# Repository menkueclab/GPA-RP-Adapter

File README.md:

# GPA-RP-Adapter
This is a shield for the red pitaya (rp-122 or rp-125) to connect it easily to the GPA-FHDO.

# Parts
- pin header
- RJ45 connector
- schmitt trigger (optional)
- SMA connector  (optional)
- capacitor  (optional)
- fan (optional)

for details see KiCad schematic.

# Contributing
Benjamin Menkuec

# Disclaimer
Not intended for medical use!

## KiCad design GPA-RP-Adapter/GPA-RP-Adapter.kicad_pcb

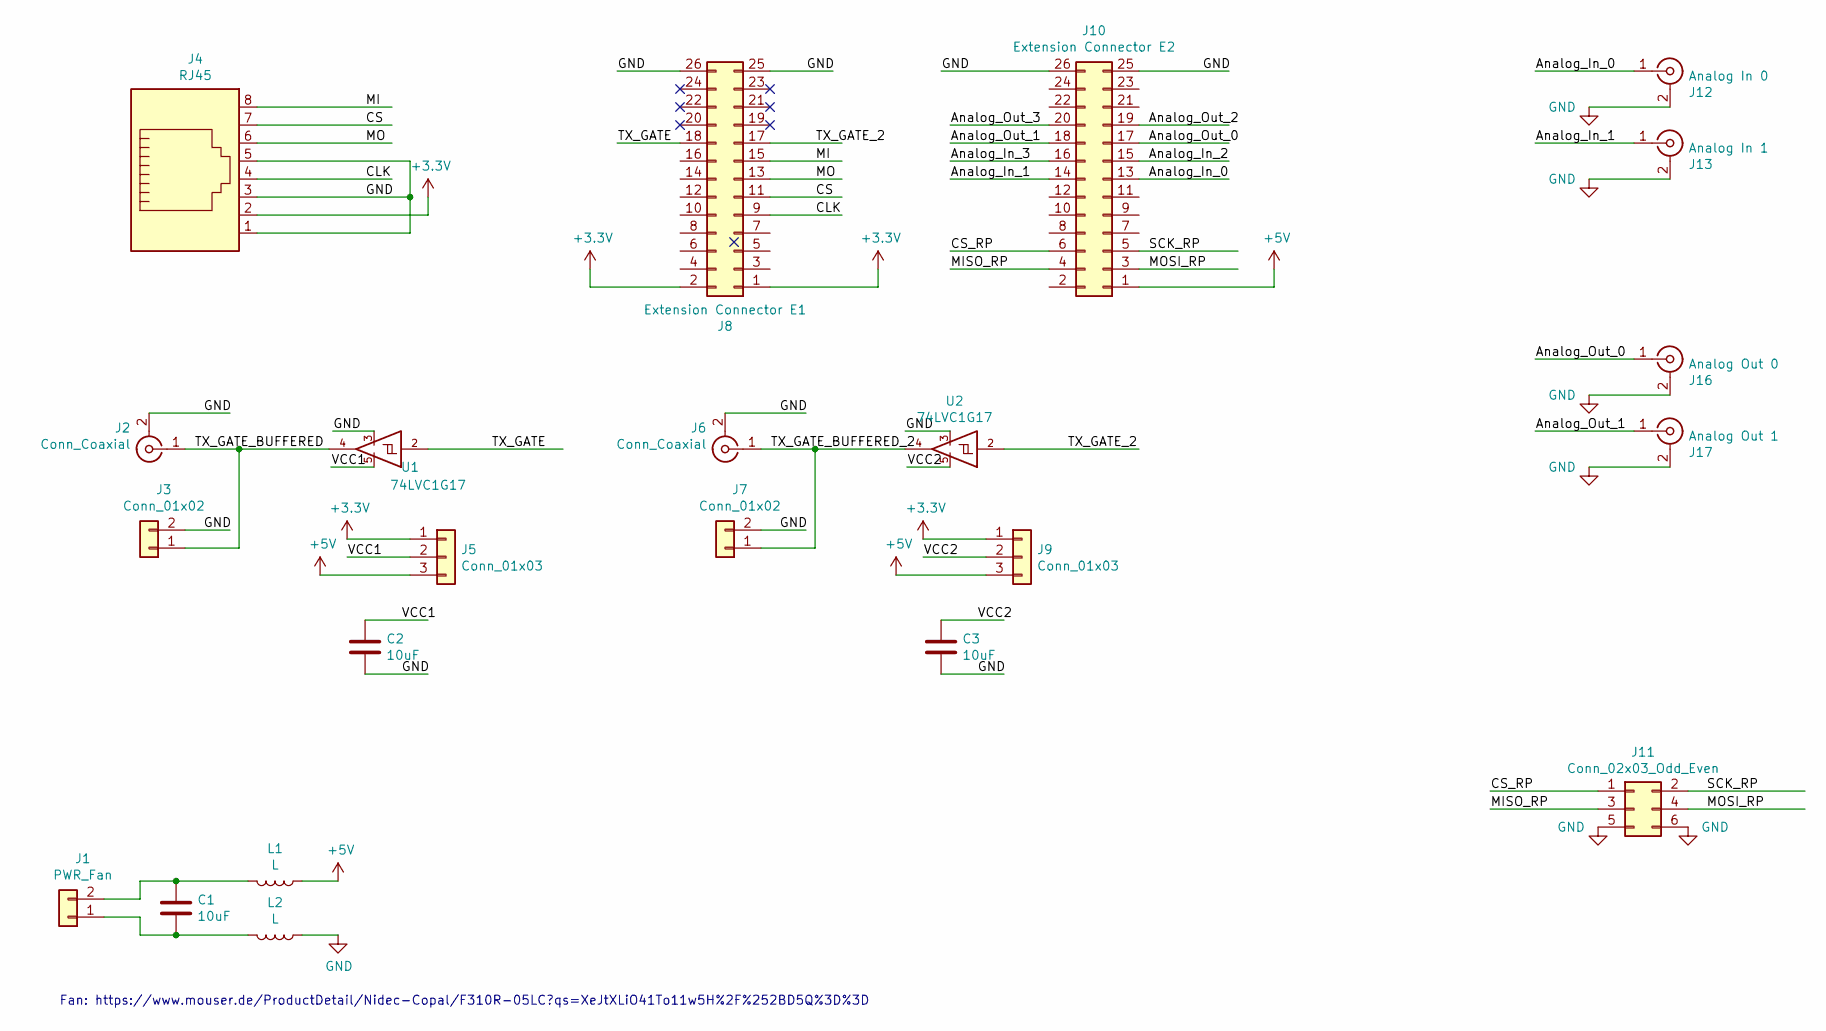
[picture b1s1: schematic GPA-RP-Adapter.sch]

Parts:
C1, C2, C3: 10uF; C_0805_2012Metric_Pad1.15x1.40mm_HandSolder
J1: PWR_Fan; PinHeader_1x02_P2.54mm_Vertical
J2, J6: Conn_Coaxial; SMA_Amphenol_132134_Vertical
J3, J7: Conn_01x02; PinHeader_1x02_P2.54mm_Vertical
J4: RJ45; RJ45_Amphenol_54602-x08_Horizontal
J5, J9: Conn_01x03; PinHeader_1x03_P2.54mm_Vertical
J8: Extension Connector E1; PinHeader_2x13_P2.54mm_Vertical
J10: Extension Connector E2; PinHeader_2x13_P2.54mm_Vertical
J11: Conn_02x03_Odd_Even; PinHeader_2x03_P2.54mm_Vertical
J12: Analog In 0; SMA_Amphenol_132134_Vertical
J13: Analog In 1; SMA_Amphenol_132134_Vertical
J16: Analog Out 0; SMA_Amphenol_132134_Vertical
J17: Analog Out 1; SMA_Amphenol_132134_Vertical
L1, L2: L; L_0805_2012Metric_Pad1.15x1.40mm_HandSolder
U1, U2: 74LVC1G17; SOT-23-5_HandSoldering

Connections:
+3V3: J4.2, J5.1, J8.1, J8.2, J9.1; also elsewhere on the board
+5V: J5.3, J9.3, J10.1, L1.1; also elsewhere on the board
/Analog_In_0: J10.13, J12.1 (In); also elsewhere on the board
/Analog_In_1: J10.14, J13.1 (In); also elsewhere on the board
/Analog_Out_0: J10.17, J16.1 (In); also elsewhere on the board
/Analog_Out_1: J10.18, J17.1 (In); also elsewhere on the board
/CLK: J4.4, J8.9; also elsewhere on the board
/CS: J4.7, J8.11; also elsewhere on the board
/CS_RP: J10.6, J11.1; also elsewhere on the board
/MI: J4.8, J8.15; also elsewhere on the board
/MISO_RP: J10.4, J11.3; also elsewhere on the board
/MO: J4.6, J8.13; also elsewhere on the board
/MOSI_RP: J10.3, J11.4; also elsewhere on the board
/SCK_RP: J10.5, J11.2; also elsewhere on the board
/TX_GATE: J8.18, U1.2; also elsewhere on the board
/TX_GATE_2: J8.17, U2.2; also elsewhere on the board
/TX_GATE_BUFFERED: J2.1 (In), J3.1, U1.4
/TX_GATE_BUFFERED_2: J6.1 (In), J7.1, U2.4
/VCC1: C2.1, J5.2, U1.5
/VCC2: C3.1, J9.2, U2.5
GND: C2.2, C3.2, J2.2 (Ext), J3.2, J4.1, J4.3, J4.5, J6.2 (Ext), J7.2, J8.25, J8.26, J10.25, J10.26, J11.5, J11.6, J12.2 (Ext), J13.2 (Ext), J16.2 (Ext), J17.2 (Ext), L2.1, U1.3, U2.3; also elsewhere on the board
unnamed: C1.1, J1.2, L1.2
unnamed: C1.2, J1.1, L2.2

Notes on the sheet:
Fan: https://www.mouser.de/ProductDetail/Nidec-Copal/F310R-05LC?qs=XeJtXLiO41To11w5H%2F%252BD5Q%3D%3D

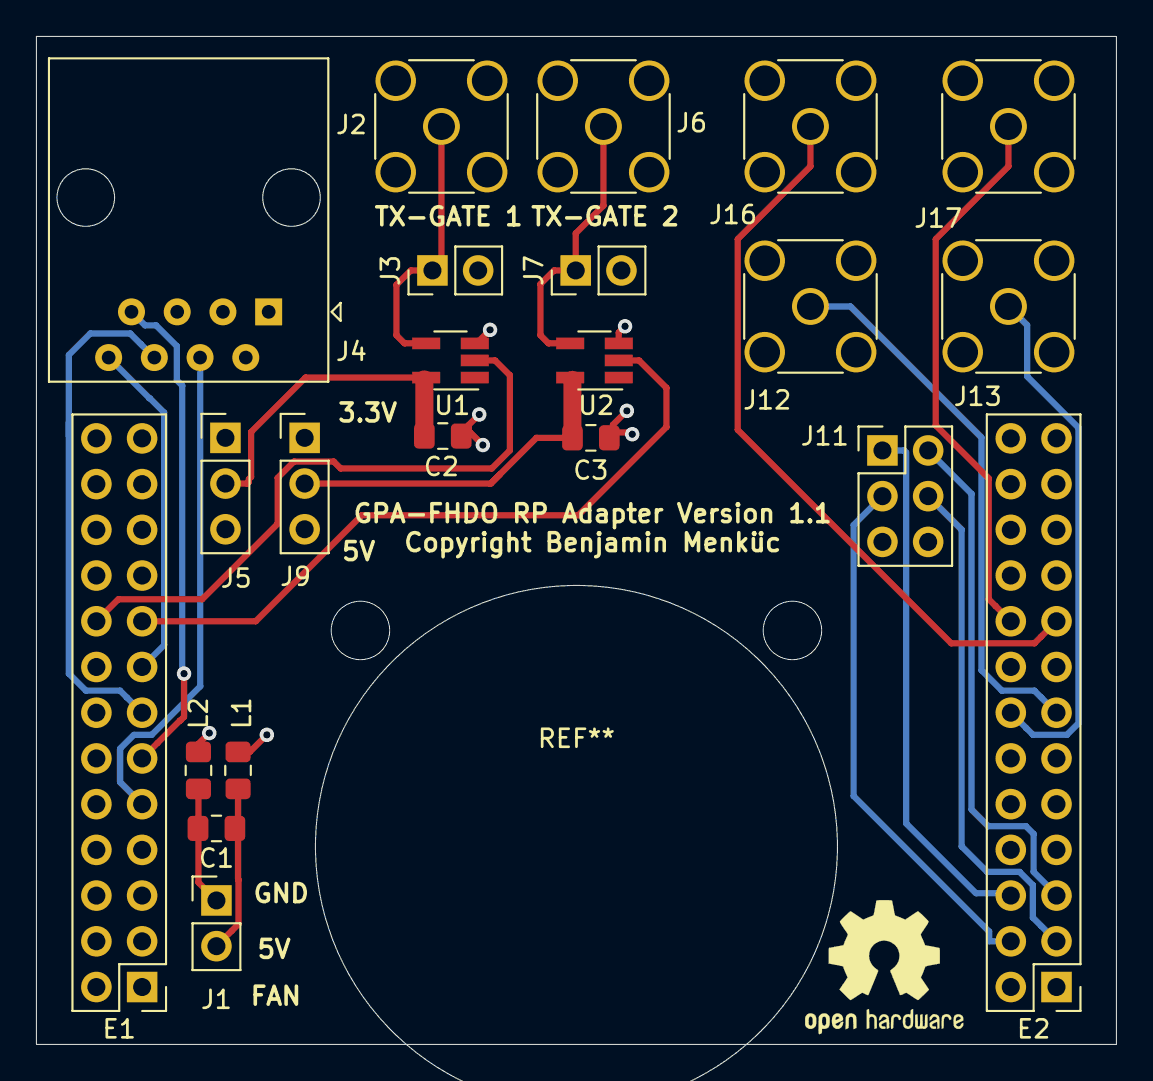
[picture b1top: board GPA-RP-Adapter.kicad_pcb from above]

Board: 4 copper layers, 60.0 x 56.0 mm, 22 parts (0 on the bottom side), 23 nets.

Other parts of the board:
E1: Extension Connector E1; PinHeader_2x13_P2.54mm_Vertical
E2: Extension Connector E2; PinHeader_2x13_P2.54mm_Vertical

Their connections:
+3V3: E1.1, E1.2; also elsewhere on the board
+5V: E2.1; also elsewhere on the board
/Analog_In_0: E2.13; also elsewhere on the board
/Analog_In_1: E2.14; also elsewhere on the board
/Analog_Out_0: E2.17; also elsewhere on the board
/Analog_Out_1: E2.18; also elsewhere on the board
/CLK: E1.9; also elsewhere on the board
/CS: E1.11; also elsewhere on the board
/CS_RP: E2.6; also elsewhere on the board
/MI: E1.15; also elsewhere on the board
/MISO_RP: E2.4; also elsewhere on the board
/MO: E1.13; also elsewhere on the board
/MOSI_RP: E2.3; also elsewhere on the board
/SCK_RP: E2.5; also elsewhere on the board
/TX_GATE: E1.18; also elsewhere on the board
/TX_GATE_2: E1.17; also elsewhere on the board
GND: E1.25, E1.26, E2.25, E2.26; also elsewhere on the board

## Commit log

2020-10-12 completed schematic
2020-10-12 added 2nd tx_gate
2020-10-12 added analog IOs, SPI and fan
2020-10-12 added PWR connector for fan
2020-10-15 finished layout
2020-11-11 fixed some errors in layout - rotated rj45 connector - connected the 5V layer properly
2023-07-25 add license

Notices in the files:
GPA-RP-Adapter/GPA-RP-Adapter.kicad_pcb:
Copyright Benjamin Menküc
